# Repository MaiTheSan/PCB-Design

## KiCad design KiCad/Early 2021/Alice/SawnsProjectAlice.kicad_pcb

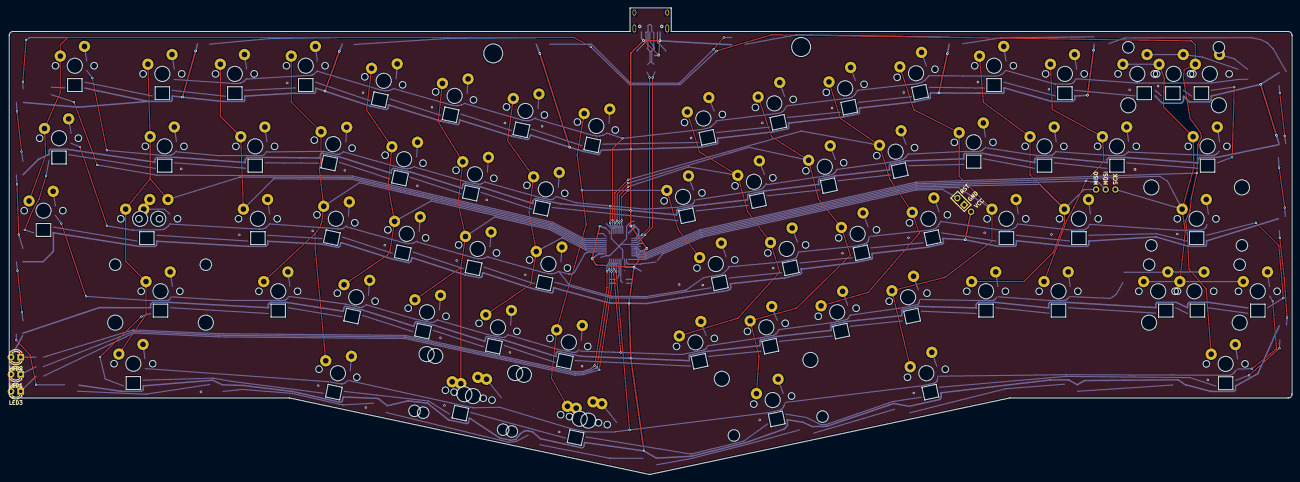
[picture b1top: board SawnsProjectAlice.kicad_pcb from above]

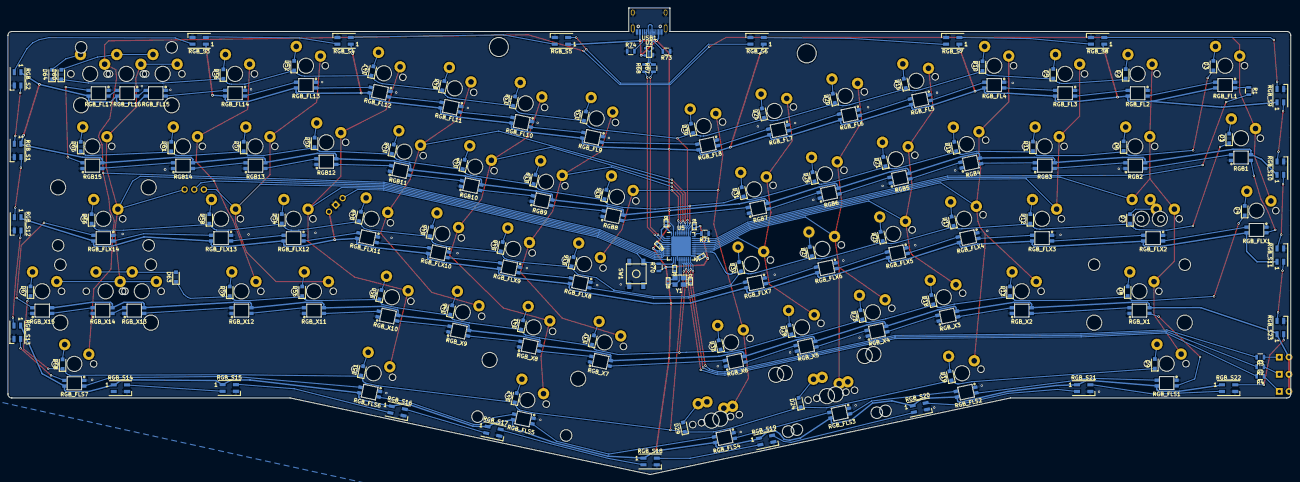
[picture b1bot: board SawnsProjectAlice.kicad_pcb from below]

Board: 2 copper layers, 337.2 x 122.6 mm, 255 parts (179 on the bottom side), 197 nets.

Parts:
C2: 10uF; SMD-0402
C3, C4, C5: 0.1uF; SMD-0402
C6: 1uF; SMD-0402
C7, C8: 22pF; SMD-0402
D1, D2, D3, D4, D5, D6, D7, D8, D9, D10, D11, D12, D13, D15, D16, D17, D18, D19, D20, D21, D22, D23, D24, D25, D26, D27, D28, D29, D30, D31, D32, D33, D34, D35, D36, D37, D38, D39, D40, D41, D42, D43, D44, D45, D46, D47, D48, D49, D50, D51, D52, D53, D54, D55, D56, D57, D58, D59, D60, D61, D63, D64, D65, D66, D67, D68: SOD_123; D_SOD-323_HandSoldering
K_0, K_1, K_2, K_3, K_4, K_5, K_6, K_7, K_8, K_9, K_.1: 1U; MXOnly-1U-NoLED
K_'1: 1U; MXOnly-1U-NoLED
K_+1: 1U; MXOnly-1U-NoLED
K_,1: 1U; MXOnly-1U-NoLED
K_-_1: 1U; MXOnly-1U-NoLED
K_/?/1: 1U; MXOnly-1U-NoLED
K_;1: 1U; MXOnly-1U-NoLED
K_A1: 1U; MXOnly-1U-NoLED
K_Alt1: 1.25U; MXOnly-1.25U-NoLED
K_B1: 1U; MXOnly-1U-NoLED
K_BkSp1: 1U; MXOnly-1U-NoLED
K_BkSp2: 2U_FL; MXOnly-2U-NoLED
K_C1: 1U; MXOnly-1U-NoLED
K_CapLk1, K_CapLk2: MX-1U-MX_Alps_Hybrids; MXOnly-1U-NoLED
K_D1: 1U; MXOnly-1U-NoLED
K_Delete1: 1U; MXOnly-1U-NoLED
K_E1: 1U; MXOnly-1U-NoLED
K_ESC1: 1U; MXOnly-1U-NoLED
K_Enter1: 2.25U; MXOnly-2.25U-ReversedStabilizers-NoLED
K_F1: 1U; MXOnly-1U-NoLED
K_FN1: 1U; MXOnly-1U-NoLED
K_G1: 1U; MXOnly-1U-NoLED
K_H1: 1U; MXOnly-1U-NoLED
K_I1: 1U; MXOnly-1U-NoLED
K_J1: 1U; MXOnly-1U-NoLED
K_K1: 1U; MXOnly-1U-NoLED
K_L1: 1U; MXOnly-1U-NoLED
K_LControl1: 1.5U; MXOnly-1.5U-NoLED
K_LShift1: MX-1U-MX_Alps_Hybrids; MXOnly-2.25U-NoLED
K_M1: 1U; MXOnly-1U-NoLED
K_N1: 1U; MXOnly-1U-NoLED
K_O1: 1U; MXOnly-1U-NoLED
K_P1: 1U; MXOnly-1U-NoLED
K_PgDn1: 1U; MXOnly-1U-NoLED
K_PgUp1: 1U; MXOnly-1U-NoLED
K_Q1: 1U; MXOnly-1U-NoLED
K_R1: 1U; MXOnly-1U-NoLED
K_RSHIFT3: 1U; MXOnly-1U-NoLED
K_RShift1: 1.75U; MXOnly-1.75U-NoLED
K_RShift2: 2.75U; MXOnly-2.75U-NoLED
K_S1: 1U; MXOnly-1U-NoLED
K_T1: 1U; MXOnly-1U-NoLED
K_Tab1: 1.5U; MXOnly-1.5U-NoLED
K_U1: 1U; MXOnly-1U-NoLED
K_V1: 1U; MXOnly-1U-NoLED
K_W1: 1U; MXOnly-1U-NoLED
K_X1: 1U; MXOnly-1U-NoLED
K_Y1: 1U; MXOnly-1U-NoLED
K_Z1: 1U; MXOnly-1U-NoLED
K_]}1: 1U; MXOnly-1U-NoLED
K_`1: 1U; MXOnly-1U-NoLED
K_{[1: 1U; MXOnly-1U-NoLED
K_|\1: 1.5U; MXOnly-1.5U-NoLED
LED1, LED2, LED3: LED; LED_D3.0mm
MX1, MX1_1: 2U; MXOnly-2U-ReversedStabilizers-NoLED
MX2, MX2_1, MX4: MX-1U-MX_Alps_Hybrids; MXOnly-1U-NoLED
MX3: 2.75U; MXOnly-2.75U-ReversedStabilizers-NoLED
MX5: 1.5U; MXOnly-1.5U-NoLED
R1: 500; R_0805
R2, R3, R4: 300; R_0805
R67, R68: 22; R_0805
R70: 10k; R_0805
R71: 1k; R_0805
R73, R74: 5.1k; R_0805
RGB1, RGB2, RGB3, RGB4, RGB5, RGB6, RGB7, RGB8, RGB9, RGB10, RGB11, RGB12, RGB13, RGB14, RGB15: WS2812B_F; RGB-6028
RGB_FL1, RGB_FL2, RGB_FL3, RGB_FL4, RGB_FL5, RGB_FL6, RGB_FL7, RGB_FL8, RGB_FL9, RGB_FL10, RGB_FL11, RGB_FL12, RGB_FL13, RGB_FL14, RGB_FL15, RGB_FL16, RGB_FL17: WS2812B; RGB-6028_FLIPPED
RGB_FLS1, RGB_FLS2, RGB_FLS3, RGB_FLS4, RGB_FLS5: WS2812B; RGB-6028_FLIPPED
RGB_FLS6, RGB_FLS7: WS2812B_S; RGB-6028_FLIPPED
RGB_FLX1, RGB_FLX2, RGB_FLX3, RGB_FLX4, RGB_FLX5, RGB_FLX6, RGB_FLX7: WS2812B; RGB-6028_FLIPPED
RGB_FLX8, RGB_FLX9, RGB_FLX10, RGB_FLX11, RGB_FLX12, RGB_FLX13, RGB_FLX14: WS2812B_F; RGB-6028_FLIPPED
RGB_S1, RGB_S2, RGB_S3, RGB_S4, RGB_S5, RGB_S6, RGB_S7, RGB_S8, RGB_S9, RGB_S10, RGB_S11, RGB_S12, RGB_S13, RGB_S14, RGB_S15, RGB_S16, RGB_S17, RGB_S18, RGB_S19, RGB_S20, RGB_S21, RGB_S22, RGB_S23: WS2812B_S; LED_SK6812MINI_PLCC4_3.5x3.5mm_P1.75mm
RGB_X1, RGB_X2, RGB_X3, RGB_X4, RGB_X5, RGB_X6, RGB_X7, RGB_X8, RGB_X9, RGB_X10, RGB_X11, RGB_X12, RGB_X13, RGB_X14, RGB_X15: WS2812B; RGB-6028
SW1: 5.2x5.2mm; SKQG-1155865
U2: PRTR5V0U2X; SOT143B
U3, U4: STF202-22T1G; Reset_Pretty
U5: ATmega32U4-MU; QFN-44-1EP_7x7mm_P0.5mm_EP5.2x5.2mm
USB1: HRO-TYPE-C-31-M-12; HRO-TYPE-C-31-M-12-Assembly
Y1: 16Mhz; Crystal_SMD_3225-4Pin_3.2x2.5mm

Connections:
+5V: C2.2, C3.2, C4.2, C5.2, LED1.2, LED2.2, LED3.2, R70.1, RGB1.1, RGB2.1, RGB3.1, RGB4.1, RGB5.1, RGB6.1, RGB7.1, RGB8.1, RGB9.1, RGB10.1, RGB11.1, RGB12.1, RGB13.1, RGB14.1, RGB15.1, RGB_FL1.1, RGB_FL2.1, RGB_FL3.1, RGB_FL4.1, RGB_FL5.1, RGB_FL6.1, RGB_FL7.1, RGB_FL8.1, RGB_FL9.1, RGB_FL10.1, RGB_FL11.1, RGB_FL12.1, RGB_FL13.1, RGB_FL14.1, RGB_FL15.1, RGB_FL16.1, RGB_FL17.1, RGB_FLS1.1, RGB_FLS2.1, RGB_FLS3.1, RGB_FLS4.1, RGB_FLS5.1, RGB_FLS6.1, RGB_FLS7.1, RGB_FLX1.1, RGB_FLX2.1, RGB_FLX3.1, RGB_FLX4.1, RGB_FLX5.1, RGB_FLX6.1, RGB_FLX7.1, RGB_FLX8.1, RGB_FLX9.1, RGB_FLX10.1, RGB_FLX11.1, RGB_FLX12.1, RGB_FLX13.1, RGB_FLX14.1, RGB_S1.1, RGB_S2.1, RGB_S3.1, RGB_S4.1, RGB_S5.1, RGB_S6.1, RGB_S7.1, RGB_S8.1, RGB_S9.1, RGB_S10.1, RGB_S11.1, RGB_S12.1, RGB_S13.1, RGB_S14.1, RGB_S15.1, RGB_S16.1, RGB_S17.1, RGB_S18.1, RGB_S19.1, RGB_S20.1, RGB_S21.1, RGB_S22.1, RGB_S23.1, RGB_X1.1, RGB_X2.1, RGB_X3.1, RGB_X4.1, RGB_X5.1, RGB_X6.1, RGB_X7.1, RGB_X8.1, RGB_X9.1, RGB_X10.1, RGB_X11.1, RGB_X12.1, RGB_X13.1, RGB_X14.1, RGB_X15.1, U2.4, U4.2, U5.2, U5.7, U5.14, U5.24, U5.34, U5.44, USB1.2, USB1.11
CapLk: R2.2, U5.21
Col0: K_CapLk1.2, K_CapLk2.1, K_LControl1.1, K_LShift1.1, K_Tab1.1, K_`1.1, U5.31
Col1: K_1.1, K_A1.1, K_Q1.1, U5.30
Col2: K_2.1, K_Alt1.1, K_S1.1, K_W1.1, K_Z1.1, U5.29
Col3: K_3.1, K_D1.1, K_E1.1, K_X1.1, U5.28
Col4: K_4.1, K_C1.1, K_F1.1, K_R1.1, MX1.1, MX1_1.1, U5.27
Col5: K_5.1, K_G1.1, K_T1.1, K_V1.1, U5.26
Col6: K_6.1, K_B1.1, K_H1.1, K_Y1.1, MX2.1, MX2_1.1, U5.41
Col7: K_7.1, K_J1.1, K_N1.1, K_U1.1, U5.40
Col8: K_8.1, K_I1.1, K_K1.1, K_M1.1, MX3.1, U5.39
Col9: K_9.1, K_,1.1, K_L1.1, K_O1.1, U5.38
Col10: K_0.1, K_.1.1, K_;1.1, K_P1.1, MX4.1, U5.12
Col11: K_'1.1, K_-_1.1, K_/?/1.1, K_{[1.1, U3.1, U5.11
Col12: K_+1.1, K_RSHIFT3.1, K_]}1.1, U3.4, U5.10
Col13: K_BkSp1.1, K_BkSp2.1, K_Enter1.1, K_FN1.1, K_RShift1.1, K_RShift2.1, K_|\1.1, U3.3, U5.9
Col14: K_Delete1.1, K_ESC1.1, K_PgDn1.1, K_PgUp1.1, MX5.1, U5.8
D+: R68.1, U5.4
D-: R67.1, U5.3
GND: C2.1, C3.1, C4.1, C5.1, C6.2, C7.2, C8.2, R71.1, R73.1, R74.1, RGB1.3, RGB2.3, RGB3.3, RGB4.3, RGB5.3, RGB6.3, RGB7.3, RGB8.3, RGB9.3, RGB10.3, RGB11.3, RGB12.3, RGB13.3, RGB14.3, RGB15.3, RGB_FL1.3, RGB_FL2.3, RGB_FL3.3, RGB_FL4.3, RGB_FL5.3, RGB_FL6.3, RGB_FL7.3, RGB_FL8.3, RGB_FL9.3, RGB_FL10.3, RGB_FL11.3, RGB_FL12.3, RGB_FL13.3, RGB_FL14.3, RGB_FL15.3, RGB_FL16.3, RGB_FL17.3, RGB_FLS1.3, RGB_FLS2.3, RGB_FLS3.3, RGB_FLS4.3, RGB_FLS5.3, RGB_FLS6.3, RGB_FLS7.3, RGB_FLX1.3, RGB_FLX2.3, RGB_FLX3.3, RGB_FLX4.3, RGB_FLX5.3, RGB_FLX6.3, RGB_FLX7.3, RGB_FLX8.3, RGB_FLX9.3, RGB_FLX10.3, RGB_FLX11.3, RGB_FLX12.3, RGB_FLX13.3, RGB_FLX14.3, RGB_S1.3, RGB_S2.3, RGB_S3.3, RGB_S4.3, RGB_S5.3, RGB_S6.3, RGB_S7.3, RGB_S8.3, RGB_S9.3, RGB_S10.3, RGB_S11.3, RGB_S12.3, RGB_S13.3, RGB_S14.3, RGB_S15.3, RGB_S16.3, RGB_S17.3, RGB_S18.3, RGB_S19.3, RGB_S20.3, RGB_S21.3, RGB_S22.3, RGB_S23.3, RGB_X1.3, RGB_X2.3, RGB_X3.3, RGB_X4.3, RGB_X5.3, RGB_X6.3, RGB_X7.3, RGB_X8.3, RGB_X9.3, RGB_X10.3, RGB_X11.3, RGB_X12.3, RGB_X13.3, RGB_X14.3, RGB_X15.3, SW1.1, U2.1, U4.6, U5.5, U5.15, U5.23, U5.35, U5.43, U5.45, USB1.1, USB1.12, USB1.13, Y1.2, Y1.4
unnamed: C6.1, U5.6
unnamed: C7.1, U5.17, Y1.1
unnamed: C8.1, U5.16, Y1.3
unnamed: D1.2, K_PgUp1.2
unnamed: D2.2, K_`1.2
unnamed: D3.2, K_ESC1.2
unnamed: D4.2, K_PgDn1.2
unnamed: D5.2, K_1.2
unnamed: D6.2, K_Tab1.2
unnamed: D7.2, K_CapLk1.1, K_CapLk2.2
unnamed: D8.2, K_LShift1.2
unnamed: D9.2, K_LControl1.2
unnamed: D10.2, K_2.2
unnamed: D11.2, K_Q1.2
unnamed: D12.2, K_A1.2
unnamed: D13.2, K_Z1.2
unnamed: D15.2, K_3.2
unnamed: D16.2, K_W1.2
unnamed: D17.2, K_S1.2
unnamed: D18.2, K_X1.2
unnamed: D19.2, K_Alt1.2
unnamed: D20.2, K_4.2
unnamed: D21.2, K_E1.2
unnamed: D22.2, K_D1.2
unnamed: D23.2, K_C1.2
unnamed: D24.2, MX1.2, MX1_1.2
unnamed: D25.2, K_5.2
unnamed: D26.2, K_R1.2
unnamed: D27.2, K_F1.2
unnamed: D28.2, K_V1.2
unnamed: D29.2, MX2.2, MX2_1.2
unnamed: D30.2, K_6.2
unnamed: D31.2, K_T1.2
unnamed: D32.2, K_G1.2
unnamed: D33.2, K_B1.2
unnamed: D34.2, K_7.2
unnamed: D35.2, K_Y1.2
unnamed: D36.2, K_H1.2
unnamed: D37.2, K_N1.2
unnamed: D38.2, K_8.2
unnamed: D39.2, K_U1.2
unnamed: D40.2, K_J1.2
unnamed: D41.2, K_M1.2
unnamed: D42.2, MX3.2
unnamed: D43.2, K_9.2
unnamed: D44.2, K_I1.2
unnamed: D45.2, K_K1.2
unnamed: D46.2, K_,1.2
unnamed: D47.2, K_0.2
unnamed: D48.2, K_O1.2
unnamed: D49.2, K_L1.2
unnamed: D50.2, K_.1.2
unnamed: D51.2, MX4.2
unnamed: D52.2, K_-_1.2
unnamed: D53.2, K_P1.2
unnamed: D54.2, K_;1.2
unnamed: D55.2, K_/?/1.2
unnamed: D56.2, K_+1.2
unnamed: D57.2, K_{[1.2
unnamed: D58.2, K_'1.2
unnamed: D59.2, K_RSHIFT3.2
unnamed: D60.2, K_BkSp1.2, K_BkSp2.2
unnamed: D61.2, K_]}1.2
unnamed: D63.2, K_RShift1.2, K_RShift2.2
unnamed: D64.2, K_Delete1.2
unnamed: D65.2, K_|\1.2
unnamed: D66.2, K_Enter1.2
unnamed: D67.2, K_FN1.2
unnamed: D68.2, MX5.2
unnamed: LED1.1, R2.1
unnamed: LED2.1, R3.1
unnamed: LED3.1, R4.1
unnamed: R1.1, RGB_FL1.4
unnamed: R67.2, U2.2, USB1.5, USB1.7
unnamed: R68.2, U2.3, USB1.6, USB1.8
unnamed: R70.2, SW1.2, U4.5, U5.13
unnamed: R71.2, U5.33
unnamed: R73.2, USB1.4
unnamed: R74.2, USB1.10
unnamed: RGB1.2, RGB_FLX1.4
unnamed: RGB1.4, RGB2.2
unnamed: RGB2.4, RGB3.2
unnamed: RGB3.4, RGB4.2
unnamed: RGB4.4, RGB5.2
unnamed: RGB5.4, RGB6.2
unnamed: RGB6.4, RGB7.2
unnamed: RGB7.4, RGB8.2
unnamed: RGB8.4, RGB9.2
unnamed: RGB9.4, RGB10.2
unnamed: RGB10.4, RGB11.2
unnamed: RGB11.4, RGB12.2
unnamed: RGB12.4, RGB13.2
unnamed: RGB13.4, RGB14.2
unnamed: RGB14.4, RGB15.2
unnamed: RGB15.4, RGB_FL17.2
unnamed: RGB_FL1.2, RGB_FL2.4
unnamed: RGB_FL2.2, RGB_FL3.4
unnamed: RGB_FL3.2, RGB_FL4.4
unnamed: RGB_FL4.2, RGB_FL5.4
unnamed: RGB_FL5.2, RGB_FL6.4
unnamed: RGB_FL6.2, RGB_FL7.4
unnamed: RGB_FL7.2, RGB_FL8.4
unnamed: RGB_FL8.2, RGB_FL9.4
unnamed: RGB_FL10.2, RGB_FL11.4
unnamed: RGB_FL9.2, RGB_FL10.4
unnamed: RGB_FL11.2, RGB_FL12.4
unnamed: RGB_FL12.2, RGB_FL13.4
unnamed: RGB_FL13.2, RGB_FL14.4
unnamed: RGB_FL14.2, RGB_FL15.4
unnamed: RGB_FL15.2, RGB_FL16.4
unnamed: RGB_FL16.2, RGB_FL17.4
unnamed: RGB_FLS1.2, RGB_FLS2.4
unnamed: RGB_FLS1.4, RGB_X1.2
unnamed: RGB_FLS2.2, RGB_FLS3.4
unnamed: RGB_FLS3.2, RGB_FLS4.4
unnamed: RGB_FLS4.2, RGB_FLS5.4
unnamed: RGB_FLS5.2, RGB_FLS6.4
unnamed: RGB_FLS6.2, RGB_FLS7.4
unnamed: RGB_FLS7.2, RGB_S13.4
unnamed: RGB_FLX1.2, RGB_FLX2.4
unnamed: RGB_FLX2.2, RGB_FLX3.4
unnamed: RGB_FLX3.2, RGB_FLX4.4
unnamed: RGB_FLX4.2, RGB_FLX5.4
unnamed: RGB_FLX5.2, RGB_FLX6.4
unnamed: RGB_FLX6.2, RGB_FLX7.4
unnamed: RGB_FLX7.2, RGB_FLX8.4
unnamed: RGB_FLX8.2, RGB_FLX9.4
unnamed: RGB_FLX10.2, RGB_FLX11.4
unnamed: RGB_FLX9.2, RGB_FLX10.4
unnamed: RGB_FLX11.2, RGB_FLX12.4
unnamed: RGB_FLX12.2, RGB_FLX13.4
unnamed: RGB_FLX13.2, RGB_FLX14.4
unnamed: RGB_FLX14.2, RGB_X15.4
unnamed: RGB_S1.2, RGB_S2.4
unnamed: RGB_S1.4, RGB_S12.2
unnamed: RGB_S2.2, RGB_S3.4
unnamed: RGB_S3.2, RGB_S4.4
unnamed: RGB_S4.2, RGB_S5.4
unnamed: RGB_S5.2, RGB_S6.4
unnamed: RGB_S6.2, RGB_S7.4
unnamed: RGB_S7.2, RGB_S8.4
unnamed: RGB_S8.2, RGB_S9.4
unnamed: RGB_S10.2, RGB_S11.4
unnamed: RGB_S9.2, RGB_S10.4
unnamed: RGB_S11.2, RGB_S23.4
unnamed: RGB_S12.4, RGB_S13.2
unnamed: RGB_S14.4, RGB_S15.2
unnamed: RGB_S15.4, RGB_S16.2
unnamed: RGB_S16.4, RGB_S17.2
unnamed: RGB_S17.4, RGB_S18.2
unnamed: RGB_S18.4, RGB_S19.2
unnamed: RGB_S19.4, RGB_S20.2
unnamed: RGB_S20.4, RGB_S21.2
unnamed: RGB_S21.4, RGB_S22.2
unnamed: RGB_S22.4, RGB_S23.2
unnamed: RGB_X1.4, RGB_X2.2
unnamed: RGB_X2.4, RGB_X3.2
unnamed: RGB_X3.4, RGB_X4.2
unnamed: RGB_X4.4, RGB_X5.2
unnamed: RGB_X5.4, RGB_X6.2
unnamed: RGB_X6.4, RGB_X7.2
unnamed: RGB_X7.4, RGB_X8.2
unnamed: RGB_X8.4, RGB_X9.2
unnamed: RGB_X9.4, RGB_X10.2
unnamed: RGB_X10.4, RGB_X11.2
unnamed: RGB_X11.4, RGB_X12.2
unnamed: RGB_X12.4, RGB_X13.2
unnamed: RGB_X13.4, RGB_X14.2
unnamed: RGB_X14.4, RGB_X15.2
NumLk: R3.2, U5.22
RGBLED: R1.2, U5.32
Row0: D2.1, D5.1, D10.1, D15.1, D20.1, D25.1, D30.1, D34.1, D38.1, D43.1, D47.1, D52.1, D56.1, D60.1, D64.1, U5.37
Row1: D3.1, D6.1, D11.1, D16.1, D21.1, D26.1, D31.1, D35.1, D39.1, D44.1, D48.1, D53.1, D57.1, D61.1, D65.1, U5.36
Row2: D1.1, D7.1, D12.1, D17.1, D22.1, D27.1, D32.1, D36.1, D40.1, D45.1, D49.1, D54.1, D58.1, D66.1, U5.25
Row3: D4.1, D8.1, D13.1, D18.1, D23.1, D28.1, D33.1, D37.1, D41.1, D46.1, D50.1, D55.1, D59.1, D63.1, U5.19
Row4: D9.1, D19.1, D24.1, D29.1, D42.1, D51.1, D67.1, D68.1, U5.18
ScLk: R4.2, U5.20

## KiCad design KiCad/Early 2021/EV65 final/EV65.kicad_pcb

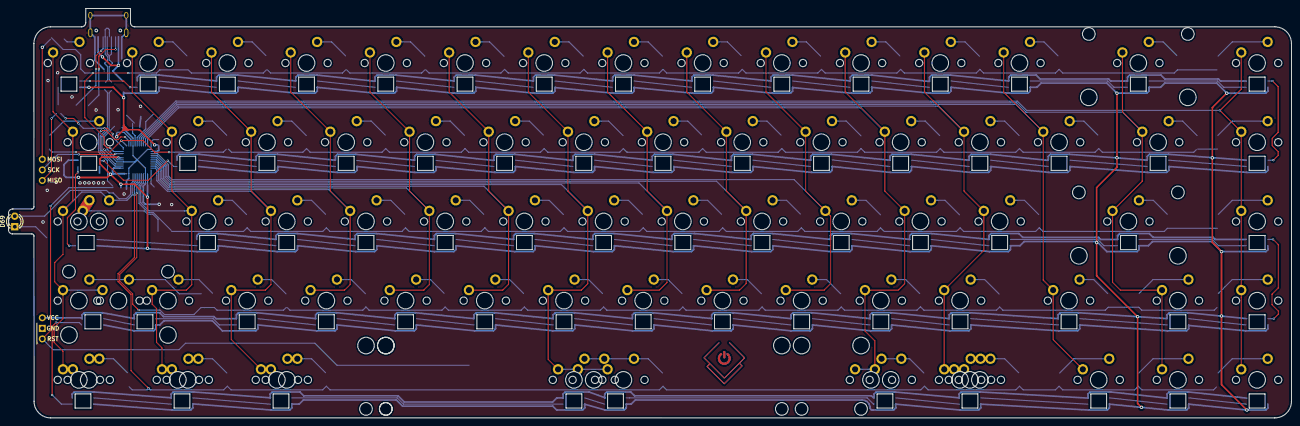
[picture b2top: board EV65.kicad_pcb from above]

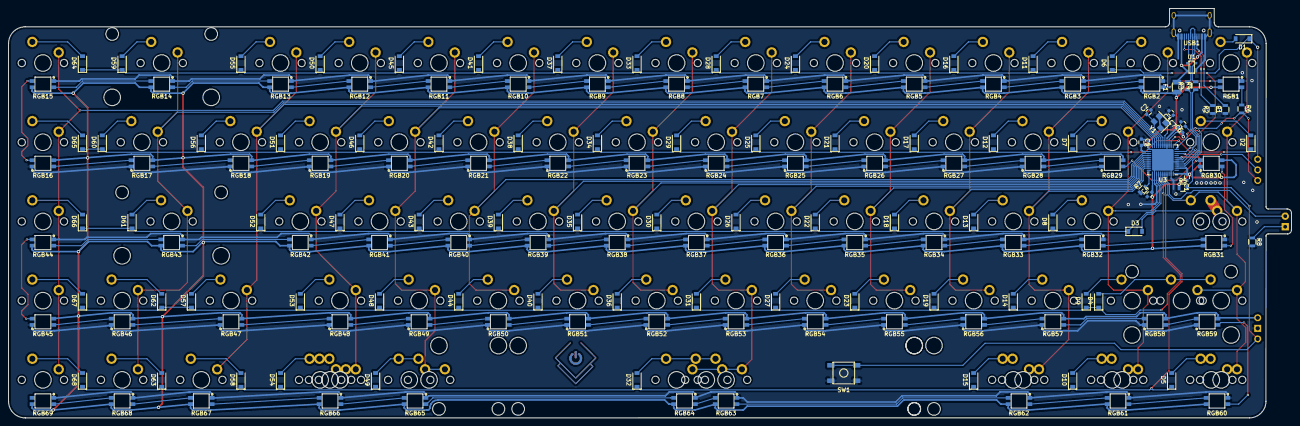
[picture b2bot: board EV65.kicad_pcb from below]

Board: 2 copper layers, 308.5 x 98.5 mm, 240 parts (158 on the bottom side), 175 nets.

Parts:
C1: 10uF; C_0603
C2, C3: 22pF; C_0603
C4, C5, C7: 0.1uF; C_0603
C6: 1uF; C_0603
D1, D2, D3, D4, D5, D6, D7, D8, D9, D10, D11, D12, D13, D14, D15, D16, D17, D18, D19, D20, D21, D22, D23, D24, D25, D26, D27, D28, D29, D30, D31, D32, D33, D34, D35, D36, D37, D38, D39, D40, D41, D42, D43, D44, D45, D46, D47, D48, D49, D50, D51, D52, D53, D54, D55, D56, D57, D58, D59, D60, D61, D62, D63, D64, D65, D66, D67, D68: D; D_SOD-123
D69: LED; LED_D3.0mm
F1: 500mA; Fuse_SMD1206_Reflow
LOGO1: LOGO; sanpjxlogo-PCB-type
MX_1, MX_6, MX_19, MX_55, MX_69: MX-1.5U-NoLED; MXOnly-1.5U-NoLED
MX_2, MX_66: MX-1.75U-NoLED; MXOnly-1.75U-NoLED
MX_3, MX_5, MX_7, MX_12, MX_18, MX_56, MX_61, MX_62: MX-1.25U-NoLED; MXOnly-1.25U-NoLED
MX_4, MX_70: MX-2.25U-NoLED; MXOnly-2.25U-NoLED
MX_8, MX_9, MX_10, MX_11, MX_13, MX_14, MX_15, MX_16, MX_17, MX_20, MX_21, MX_22, MX_23, MX_24, MX_25, MX_26, MX_27, MX_28, MX_29, MX_30, MX_31, MX_32, MX_33, MX_34, MX_35, MX_39, MX_40, MX_41, MX_42, MX_43, MX_44, MX_45, MX_46, MX_47, MX_48, MX_49, MX_50, MX_51, MX_52, MX_53, MX_54, MX_57, MX_58, MX_59, MX_60, MX_63, MX_64, MX_65, MX_67, MX_71, MX_72, MX_73, MX_74, MX_75, MX_76, MX_77: MX-NoLED; MXOnly-1U-NoLED
MX_36, MX_37: MX-6.25U-NoLED-rStab; MXOnly-6.25U-ReversedStabilizers-NoLED
MX_38: MX-7U-NoLED-rStab; MXOnly-7U-ReversedStabilizers-NoLED
MX_68: MX-2U-NoLED; MXOnly-2U-NoLED
MX_ESC1: MX-NoLED; MXOnly-1U-NoLED
R1, R2: 5.1k; R_0805
R3, R4: 22; R_0805
R5: 10k; R_0805
R6: 500; R_0805
R7: 1k; R_0805
R8: 300; R_0805
RGB1, RGB2, RGB3, RGB4, RGB5, RGB6, RGB7, RGB8, RGB9, RGB10, RGB11, RGB12, RGB13, RGB14, RGB15, RGB31, RGB32, RGB33, RGB34, RGB35, RGB36, RGB37, RGB38, RGB39, RGB40, RGB41, RGB42, RGB43, RGB44, RGB60, RGB61, RGB62, RGB63, RGB64, RGB65, RGB66, RGB67, RGB68, RGB69: WS2812B; RGB-6028_FLIPPED
RGB16, RGB17, RGB18, RGB19, RGB20, RGB21, RGB22, RGB23, RGB24, RGB25, RGB26, RGB27, RGB28, RGB29, RGB30, RGB45, RGB46, RGB47, RGB48, RGB49, RGB50, RGB51, RGB52, RGB53, RGB54, RGB55, RGB56, RGB57, RGB58, RGB59: WS2812B; RGB-6028
SW1: 5.2x5.2mm; SKQG-1155865
U1: PRTR5V0U2X; SOT143B
U2, U4: STF202-22T1G; Reset_Pretty
U3: ATmega32U4-MU; QFN-44-1EP_7x7mm_P0.5mm_EP5.2x5.2mm
USB1: HRO-TYPE-C-31-M-12; HRO-TYPE-C-31-M-12-Assembly
Y1: 16Mhz; Crystal_SMD_3225-4Pin_3.2x2.5mm

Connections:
+5V: C1.2, C4.2, C5.2, C7.2, F1.1, R5.1, RGB1.1, RGB2.1, RGB3.1, RGB4.1, RGB5.1, RGB6.1, RGB7.1, RGB8.1, RGB9.1, RGB10.1, RGB11.1, RGB12.1, RGB13.1, RGB14.1, RGB15.1, RGB16.1, RGB17.1, RGB18.1, RGB19.1, RGB20.1, RGB21.1, RGB22.1, RGB23.1, RGB24.1, RGB25.1, RGB26.1, RGB27.1, RGB28.1, RGB29.1, RGB30.1, RGB31.1, RGB32.1, RGB33.1, RGB34.1, RGB35.1, RGB36.1, RGB37.1, RGB38.1, RGB39.1, RGB40.1, RGB41.1, RGB42.1, RGB43.1, RGB44.1, RGB45.1, RGB46.1, RGB47.1, RGB48.1, RGB49.1, RGB50.1, RGB51.1, RGB52.1, RGB53.1, RGB54.1, RGB55.1, RGB56.1, RGB57.1, RGB58.1, RGB59.1, RGB60.1, RGB61.1, RGB62.1, RGB63.1, RGB64.1, RGB65.1, RGB66.1, RGB67.1, RGB68.1, RGB69.1, U3.2, U3.7, U3.14, U3.24, U3.34, U3.44, U4.2
/SCK: U2.3, U3.9
Caplsk: D69.2, U3.41
Col0: MX_1.1, MX_2.2, MX_3.1, MX_4.1, MX_5.1, MX_6.1, MX_7.1, MX_ESC1.1, U3.40
Col1: MX_8.1, MX_9.1, MX_10.1, MX_11.1, MX_12.1, MX_13.1, U3.36
Col2: MX_14.1, MX_15.1, MX_16.1, MX_17.1, MX_18.1, MX_19.1, U3.32
Col3: MX_20.1, MX_21.1, MX_22.1, MX_23.1, U3.31
Col4: MX_24.1, MX_25.1, MX_26.1, MX_27.1, U3.30
Col5: MX_28.1, MX_29.1, MX_30.1, MX_31.1, U3.29
Col6: MX_32.1, MX_33.1, MX_34.1, MX_35.1, MX_36.1, MX_37.1, MX_38.1, U3.28
Col7: MX_39.1, MX_40.1, MX_41.1, MX_42.1, U3.27
Col8: MX_43.1, MX_44.1, MX_45.1, MX_46.1, U3.26
Col9: MX_47.1, MX_48.1, MX_49.1, MX_50.1, U3.25
Col10: MX_51.1, MX_52.1, MX_53.1, MX_54.1, MX_56.1, MX_62.1, U3.22
Col11: MX_55.1, MX_57.1, MX_58.1, MX_59.1, MX_60.1, MX_61.1, MX_63.1, U3.21
Col12: MX_64.1, MX_65.1, MX_66.1, MX_67.1, U3.20
Col13: MX_68.1, MX_69.1, MX_70.1, MX_71.1, MX_72.1, U3.19
Col14: MX_73.1, MX_74.1, MX_75.1, MX_76.1, MX_77.1, U3.18
D+: R3.1, U3.4
D-: R4.1, U3.3
GND: C1.1, C2.2, C3.2, C4.1, C5.1, C6.2, C7.1, R1.1, R2.1, R7.1, R8.2, RGB1.3, RGB2.3, RGB3.3, RGB4.3, RGB5.3, RGB6.3, RGB7.3, RGB8.3, RGB9.3, RGB10.3, RGB11.3, RGB12.3, RGB13.3, RGB14.3, RGB15.3, RGB16.3, RGB17.3, RGB18.3, RGB19.3, RGB20.3, RGB21.3, RGB22.3, RGB23.3, RGB24.3, RGB25.3, RGB26.3, RGB27.3, RGB28.3, RGB29.3, RGB30.3, RGB31.3, RGB32.3, RGB33.3, RGB34.3, RGB35.3, RGB36.3, RGB37.3, RGB38.3, RGB39.3, RGB40.3, RGB41.3, RGB42.3, RGB43.3, RGB44.3, RGB45.3, RGB46.3, RGB47.3, RGB48.3, RGB49.3, RGB50.3, RGB51.3, RGB52.3, RGB53.3, RGB54.3, RGB55.3, RGB56.3, RGB57.3, RGB58.3, RGB59.3, RGB60.3, RGB61.3, RGB62.3, RGB63.3, RGB64.3, RGB65.3, RGB66.3, RGB67.3, RGB68.3, RGB69.3, SW1.1, U1.1, U3.5, U3.15, U3.23, U3.35, U3.43, U3.45, U4.6, USB1.1, USB1.12, USB1.13, Y1.2, Y1.4
unnamed: C2.1, U3.17, Y1.3
unnamed: C3.1, U3.16, Y1.1
unnamed: C6.1, U3.6
unnamed: D1.2, MX_ESC1.2
unnamed: D2.2, MX_1.2
unnamed: D3.2, MX_2.1, MX_7.2
unnamed: D4.2, MX_3.2, MX_4.2
unnamed: D5.2, MX_5.2, MX_6.2
unnamed: D6.2, MX_8.2
unnamed: D7.2, MX_9.2
unnamed: D8.2, MX_10.2
unnamed: D9.2, MX_11.2
unnamed: D10.2, MX_12.2, MX_13.2
unnamed: D11.2, MX_14.2
unnamed: D12.2, MX_15.2
unnamed: D13.2, MX_16.2
unnamed: D14.2, MX_17.2
unnamed: D15.2, MX_18.2, MX_19.2
unnamed: D16.2, MX_20.2
unnamed: D17.2, MX_21.2
unnamed: D18.2, MX_22.2
unnamed: D19.2, MX_23.2
unnamed: D20.2, MX_24.2
unnamed: D21.2, MX_25.2
unnamed: D22.2, MX_26.2
unnamed: D23.2, MX_27.2
unnamed: D24.2, MX_28.2
unnamed: D25.2, MX_29.2
unnamed: D26.2, MX_30.2
unnamed: D27.2, MX_31.2
unnamed: D28.2, MX_32.2
unnamed: D29.2, MX_33.2
unnamed: D30.2, MX_34.2
unnamed: D31.2, MX_35.2
unnamed: D32.2, MX_36.2, MX_37.2, MX_38.2
unnamed: D33.2, MX_39.2
unnamed: D34.2, MX_40.2
unnamed: D35.2, MX_41.2
unnamed: D36.2, MX_42.2
unnamed: D37.2, MX_43.2
unnamed: D38.2, MX_44.2
unnamed: D39.2, MX_45.2
unnamed: D40.2, MX_46.2
unnamed: D41.2, MX_47.2
unnamed: D42.2, MX_48.2
unnamed: D43.2, MX_49.2
unnamed: D44.2, MX_50.2
unnamed: D45.2, MX_51.2
unnamed: D46.2, MX_52.2
unnamed: D47.2, MX_53.2
unnamed: D48.2, MX_54.2
unnamed: D49.2, MX_56.2, MX_62.2
unnamed: D50.2, MX_57.2
unnamed: D51.2, MX_58.2
unnamed: D52.2, MX_59.2
unnamed: D53.2, MX_60.2
unnamed: D54.2, MX_55.2, MX_61.2, MX_63.2
unnamed: D55.2, MX_64.2
unnamed: D56.2, MX_65.2
unnamed: D57.2, MX_66.2
unnamed: D58.2, MX_67.2
unnamed: D59.2, MX_68.2
unnamed: D60.2, MX_69.2
unnamed: D61.2, MX_70.2
unnamed: D62.2, MX_71.2
unnamed: D63.2, MX_72.2
unnamed: D64.2, MX_73.2
unnamed: D65.2, MX_74.2
unnamed: D66.2, MX_75.2
unnamed: D67.2, MX_76.2
unnamed: D68.2, MX_77.2
unnamed: D69.1, R8.1
unnamed: R1.2, USB1.4
unnamed: R2.2, USB1.10
unnamed: R3.2, U1.3, USB1.6, USB1.8
unnamed: R4.2, U1.2, USB1.5, USB1.7
unnamed: R5.2, SW1.2, U3.13, U4.5
unnamed: R6.1, RGB1.4
unnamed: R7.2, U3.33
unnamed: RGB1.2, RGB2.4
unnamed: RGB2.2, RGB3.4
unnamed: RGB3.2, RGB4.4
unnamed: RGB4.2, RGB5.4
unnamed: RGB5.2, RGB6.4
unnamed: RGB6.2, RGB7.4
unnamed: RGB7.2, RGB8.4
unnamed: RGB8.2, RGB9.4
unnamed: RGB10.2, RGB11.4
unnamed: RGB9.2, RGB10.4
unnamed: RGB11.2, RGB12.4
unnamed: RGB12.2, RGB13.4
unnamed: RGB13.2, RGB14.4
unnamed: RGB14.2, RGB15.4
unnamed: RGB16.2, RGB17.4
unnamed: RGB17.2, RGB18.4
unnamed: RGB18.2, RGB19.4
unnamed: RGB19.2, RGB20.4
unnamed: RGB20.2, RGB21.4
unnamed: RGB21.2, RGB22.4
unnamed: RGB22.2, RGB23.4
unnamed: RGB23.2, RGB24.4
unnamed: RGB24.2, RGB25.4
unnamed: RGB25.2, RGB26.4
unnamed: RGB26.2, RGB27.4
unnamed: RGB27.2, RGB28.4
unnamed: RGB28.2, RGB29.4
unnamed: RGB29.2, RGB30.4
unnamed: RGB31.2, RGB32.4
unnamed: RGB32.2, RGB33.4
unnamed: RGB33.2, RGB34.4
unnamed: RGB34.2, RGB35.4
unnamed: RGB35.2, RGB36.4
unnamed: RGB36.2, RGB37.4
unnamed: RGB37.2, RGB38.4
unnamed: RGB38.2, RGB39.4
unnamed: RGB39.2, RGB40.4
unnamed: RGB40.2, RGB41.4
unnamed: RGB41.2, RGB42.4
unnamed: RGB42.2, RGB43.4
unnamed: RGB43.2, RGB44.4
unnamed: RGB45.2, RGB46.4
unnamed: RGB46.2, RGB47.4
unnamed: RGB47.2, RGB48.4
unnamed: RGB48.2, RGB49.4
unnamed: RGB49.2, RGB50.4
unnamed: RGB50.2, RGB51.4
unnamed: RGB51.2, RGB52.4
unnamed: RGB52.2, RGB53.4
unnamed: RGB53.2, RGB54.4
unnamed: RGB54.2, RGB55.4
unnamed: RGB55.2, RGB56.4
unnamed: RGB56.2, RGB57.4
unnamed: RGB57.2, RGB58.4
unnamed: RGB58.2, RGB59.4
unnamed: RGB60.2, RGB61.4
unnamed: RGB61.2, RGB62.4
unnamed: RGB62.2, RGB63.4
unnamed: RGB63.2, RGB64.4
unnamed: RGB64.2, RGB65.4
unnamed: RGB65.2, RGB66.4
unnamed: RGB66.2, RGB67.4
unnamed: RGB67.2, RGB68.4
unnamed: RGB68.2, RGB69.4
RGB: R6.2, U2.1, U3.11
RGB_Row1: RGB15.2, RGB16.4
RGB_Row2: RGB30.2, RGB31.4
RGB_Row3: RGB44.2, RGB45.4
RGB_Row4: RGB59.2, RGB60.4
Row0: D1.1, D6.1, D11.1, D16.1, D20.1, D24.1, D28.1, D33.1, D37.1, D41.1, D45.1, D50.1, D55.1, D59.1, D64.1, U2.4, U3.10
Row1: D2.1, D7.1, D12.1, D17.1, D21.1, D25.1, D29.1, D34.1, D38.1, D42.1, D46.1, D51.1, D56.1, D60.1, D65.1, U3.12
Row2: D3.1, D8.1, D13.1, D18.1, D22.1, D26.1, D30.1, D35.1, D39.1, D43.1, D47.1, D52.1, D61.1, D66.1, U3.37
Row3: D4.1, D9.1, D14.1, D19.1, D23.1, D27.1, D31.1, D36.1, D40.1, D44.1, D48.1, D53.1, D57.1, D62.1, D67.1, U3.38
Row4: D5.1, D10.1, D15.1, D32.1, D49.1, D54.1, D58.1, D63.1, D68.1, U3.39
VCC: F1.2, U1.4, USB1.2, USB1.11

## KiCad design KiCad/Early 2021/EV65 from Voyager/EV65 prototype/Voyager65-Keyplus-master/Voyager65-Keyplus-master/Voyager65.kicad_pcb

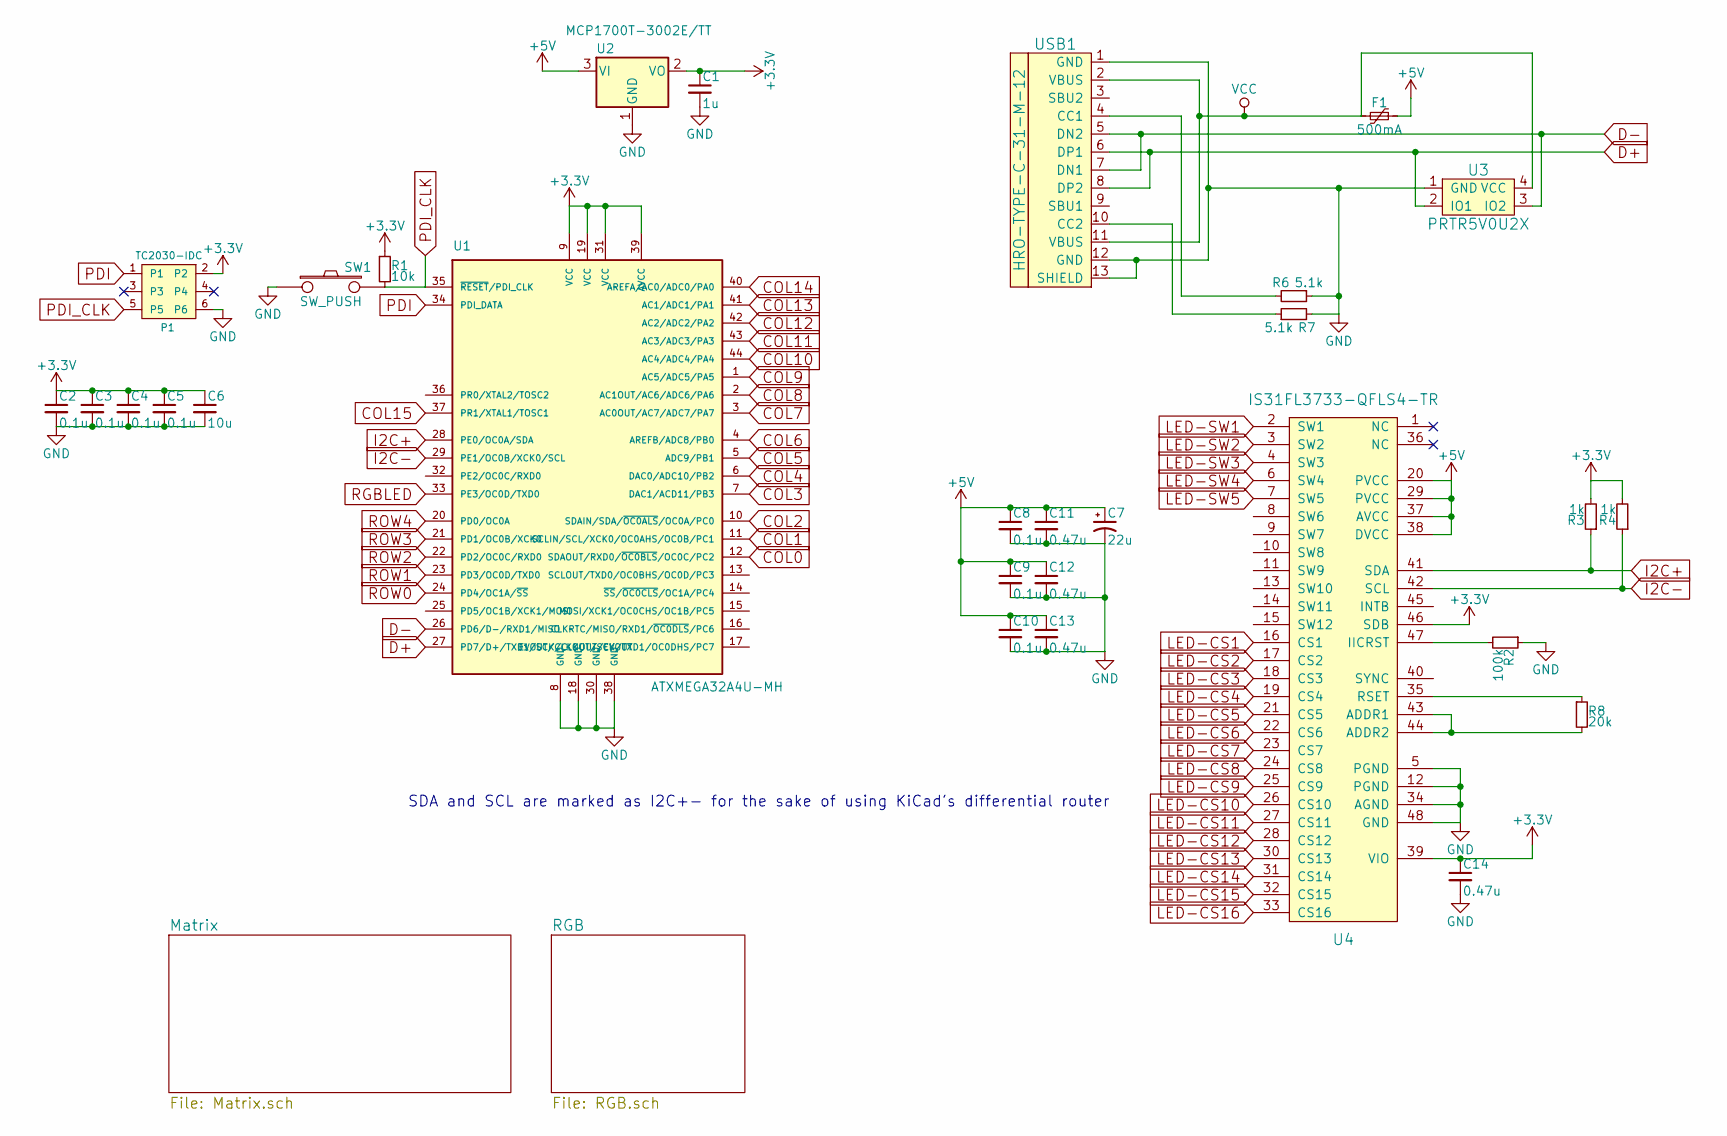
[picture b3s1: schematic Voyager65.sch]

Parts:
C1: 1u; C_0603
C2, C3, C4, C5, C8, C9, C10: 0.1u; C_0603
C6: 10u; C_0603
C7: 22u; C_0805; Voltage 10V
C11, C12, C13, C14: 0.47u; C_0603
F1: 500mA; R_0805
P1: TC2030-IDC; TC2030-NL_SMALL_AND_IDC_PDI
R1: 10k; R_0603
R2: 100k; R_0603
R3, R4: 1k; R_0603
R6, R7: 5.1k; R_0603
R8: 20k; R_0603
SW1: SW_PUSH; SKQG-1155865
U1: ATXMEGA32A4U-MH; QFN-44-1EP_7x7mm_Pitch0.5mm
U2: MCP1700T-3002E/TT; SOT-23
U3: PRTR5V0U2X; SOT143B
U4: IS31FL3733-QFLS4-TR; QFN-48-1EP_6x6mm_Pitch0.4mm
USB1: HRO-TYPE-C-31-M-12

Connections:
+3V3: C1.1, C2.1, C3.1, C4.1, C5.1, C6.1, C14.1, P1.2, R1.1, R3.2, R4.2, U1.9 (VCC), U1.19 (VCC), U1.31 (VCC), U1.39 (AVCC), U2.2 (VO), U4.39 (VIO), U4.46 (SDB)
+5V: C7.1, C8.1, C9.1, C10.1, C11.1, C12.1, C13.1, F1.1, U2.3 (VI), U4.20 (PVCC), U4.29 (PVCC), U4.37 (AVCC), U4.38 (DVCC); also elsewhere on the board
COL0: U1.12 (SDAOUT/RXD0/~OC0BLS~/OC0C/PC2); also elsewhere on the board
COL1: U1.11 (SCLIN/SCL/XCK0/OC0AHS/OC0B/PC1); also elsewhere on the board
COL2: U1.10 (SDAIN/SDA/~OC0ALS~/OC0A/PC0); also elsewhere on the board
COL3: U1.7 (DAC1/ACD11/PB3); also elsewhere on the board
COL4: U1.6 (DAC0/ADC10/PB2); also elsewhere on the board
COL5: U1.5 (ADC9/PB1); also elsewhere on the board
COL6: U1.4 (AREFB/ADC8/PB0); also elsewhere on the board
COL7: U1.3 (AC0OUT/AC7/ADC7/PA7); also elsewhere on the board
COL8: U1.2 (AC1OUT/AC6/ADC6/PA6); also elsewhere on the board
COL9: U1.1 (AC5/ADC5/PA5); also elsewhere on the board
COL10: U1.44 (AC4/ADC4/PA4); also elsewhere on the board
COL11: U1.43 (AC3/ADC3/PA3); also elsewhere on the board
COL12: U1.42 (AC2/ADC2/PA2); also elsewhere on the board
COL13: U1.41 (AC1/ADC1/PA1); also elsewhere on the board
COL14: U1.40 (AREFA/AC0/ADC0/PA0); also elsewhere on the board
COL15: U1.37 (PR1/XTAL1/TOSC1); also elsewhere on the board
D+: U1.27 (PD7/D+/TXD1/SCK/CLKOUT/EVOUT), U3.2 (IO1), USB1.6 (DP1), USB1.8 (DP2)
D-: U1.26 (PD6/D-/RXD1/MISO), U3.3 (IO2), USB1.5 (DN2), USB1.7 (DN1)
GND: C1.2, C2.2, C3.2, C4.2, C5.2, C6.2, C7.2, C8.2, C9.2, C10.2, C11.2, C12.2, C13.2, C14.2, P1.6, R2.1, R6.1, R7.2, SW1.1, U1.8 (GND), U1.18 (GND), U1.30 (GND), U1.38 (GND), U2.1 (GND), U3.1 (GND), U4.5 (PGND), U4.12 (PGND), U4.34 (AGND), U4.48 (GND), USB1.1 (GND), USB1.12 (GND), USB1.13 (SHIELD); also elsewhere on the board
I2C+: R3.1, U1.28 (PE0/OC0A/SDA), U4.41 (SDA)
I2C-: R4.1, U1.29 (PE1/OC0B/XCK0/SCL), U4.42 (SCL)
LED-CS1: U4.16 (CS1); also elsewhere on the board
LED-CS2: U4.17 (CS2); also elsewhere on the board
LED-CS3: U4.18 (CS3); also elsewhere on the board
LED-CS4: U4.19 (CS4); also elsewhere on the board
LED-CS5: U4.21 (CS5); also elsewhere on the board
LED-CS6: U4.22 (CS6); also elsewhere on the board
LED-CS7: U4.23 (CS7); also elsewhere on the board
LED-CS8: U4.24 (CS8); also elsewhere on the board
LED-CS9: U4.25 (CS9); also elsewhere on the board
LED-CS10: U4.26 (CS10); also elsewhere on the board
LED-CS11: U4.27 (CS11); also elsewhere on the board
LED-CS12: U4.28 (CS12); also elsewhere on the board
LED-CS13: U4.30 (CS13); also elsewhere on the board
LED-CS14: U4.31 (CS14); also elsewhere on the board
LED-CS15: U4.32 (CS15); also elsewhere on the board
LED-CS16: U4.33 (CS16); also elsewhere on the board
LED-SW1: U4.2 (SW1); also elsewhere on the board
LED-SW2: U4.3 (SW2); also elsewhere on the board
LED-SW3: U4.4 (SW3); also elsewhere on the board
LED-SW4: U4.6 (SW4); also elsewhere on the board
LED-SW5: U4.7 (SW5); also elsewhere on the board
unnamed: R2.2, U4.47 (IICRST)
unnamed: R6.2, USB1.4 (CC1)
unnamed: R7.1, USB1.10 (CC2)
unnamed: R8.1, U4.35 (RSET)
unnamed: R8.2, U4.43 (ADDR1), U4.44 (ADDR2)
PDI: P1.1, U1.34 (PDI_DATA)
PDI_CLK: P1.5, R1.2, SW1.2, U1.35 (~RESET~/PDI_CLK)
RGBLED: U1.33 (PE3/OC0D/TXD0); also elsewhere on the board
ROW0: U1.24 (PD4/OC1A/~SS~); also elsewhere on the board
ROW1: U1.23 (PD3/OC0D/TXD0); also elsewhere on the board
ROW2: U1.22 (PD2/OC0C/RXD0); also elsewhere on the board
ROW3: U1.21 (PD1/OC0B/XCK0); also elsewhere on the board
ROW4: U1.20 (PD0/OC0A); also elsewhere on the board
VCC: F1.2, U3.4 (VCC), USB1.2 (VBUS), USB1.11 (VBUS)

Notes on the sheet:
SDA and SCL are marked as I2C+- for the sake of using KiCad's differential router
